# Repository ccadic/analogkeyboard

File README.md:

# analogkeyboard
Small analog keyboard with 20 buttons

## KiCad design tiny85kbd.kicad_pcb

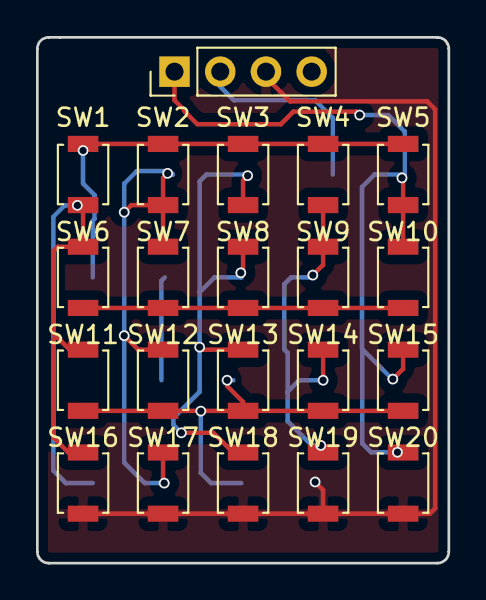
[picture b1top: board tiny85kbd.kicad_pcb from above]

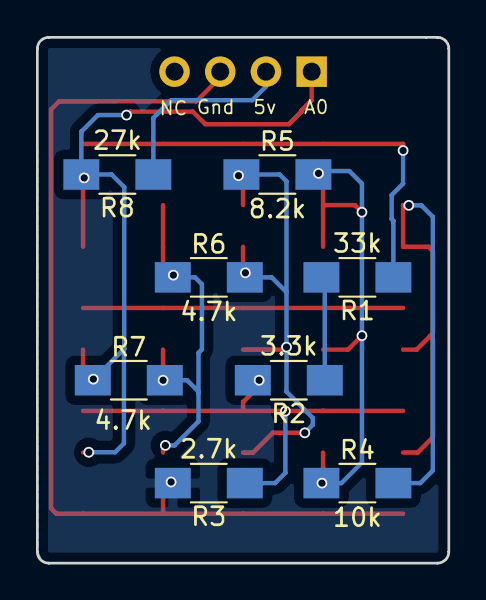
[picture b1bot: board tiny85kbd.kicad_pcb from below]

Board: 2 copper layers, 22.9 x 29.2 mm, 29 parts (8 on the bottom side), 10 nets.

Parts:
J1: AtinyCon; Socket_Strip_Straight_1x04_Pitch2.54mm
R1: 33k; R_1206_HandSoldering
R2: 3.3k; R_1206_HandSoldering
R3: 2.7k; R_1206_HandSoldering
R4: 10k; R_1206_HandSoldering
R5: 8.2k; R_1206_HandSoldering
R6, R7: 4.7k; R_1206_HandSoldering
R8: 27k; R_1206_HandSoldering
SW1, SW2, SW3, SW4, SW5, SW6, SW7, SW8, SW9, SW10, SW11, SW12, SW13, SW14, SW15, SW16, SW17, SW18, SW19, SW20: SW_Push_45deg; SW_SPST_B3U-1000P

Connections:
Analog_Input: J1.1, R7.1, R8.2, SW5.1, SW10.1, SW15.1, SW20.1
GND: J1.3, R3.2, SW16.2, SW17.2, SW18.2, SW19.2, SW20.2
unnamed: R1.1, SW1.2, SW2.2, SW3.2, SW4.2, SW5.2
unnamed: R1.2, R2.1, SW6.2, SW7.2, SW8.2, SW9.2, SW10.2
unnamed: R2.2, R3.1, SW11.2, SW12.2, SW13.2, SW14.2, SW15.2
unnamed: R4.1, R5.2, SW2.1, SW7.1, SW12.1, SW17.1
unnamed: R4.2, SW1.1, SW6.1, SW11.1, SW16.1
unnamed: R5.1, R6.2, SW3.1, SW8.1, SW13.1, SW18.1
unnamed: R6.1, R7.2, SW4.1, SW9.1, SW14.1, SW19.1
Vcc: J1.2, R8.1
